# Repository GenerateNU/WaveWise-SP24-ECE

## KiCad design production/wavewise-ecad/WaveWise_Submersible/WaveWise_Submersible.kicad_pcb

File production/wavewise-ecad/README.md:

This is where all KiCAD stuff is stored

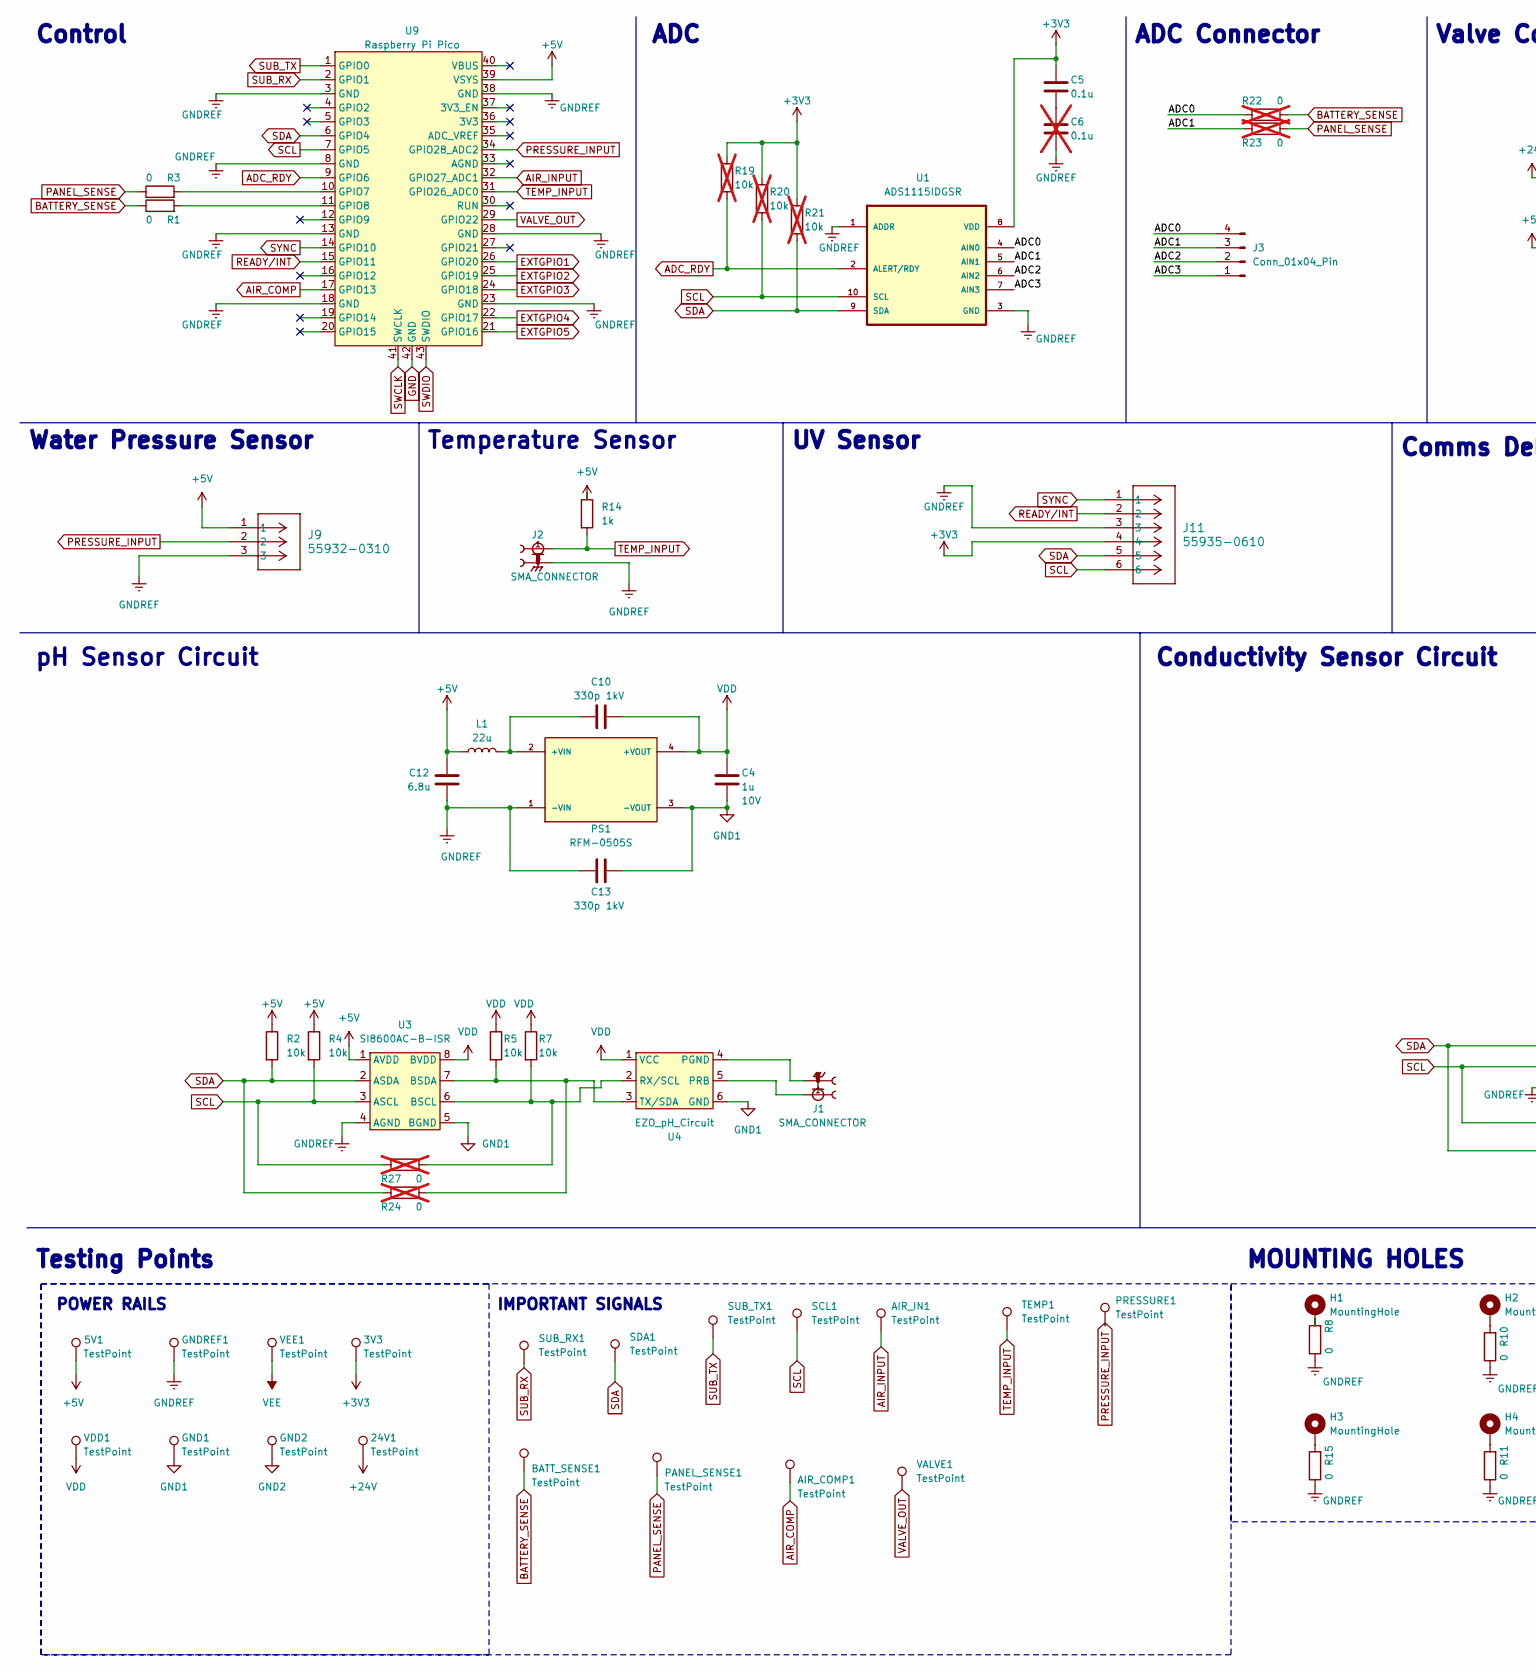
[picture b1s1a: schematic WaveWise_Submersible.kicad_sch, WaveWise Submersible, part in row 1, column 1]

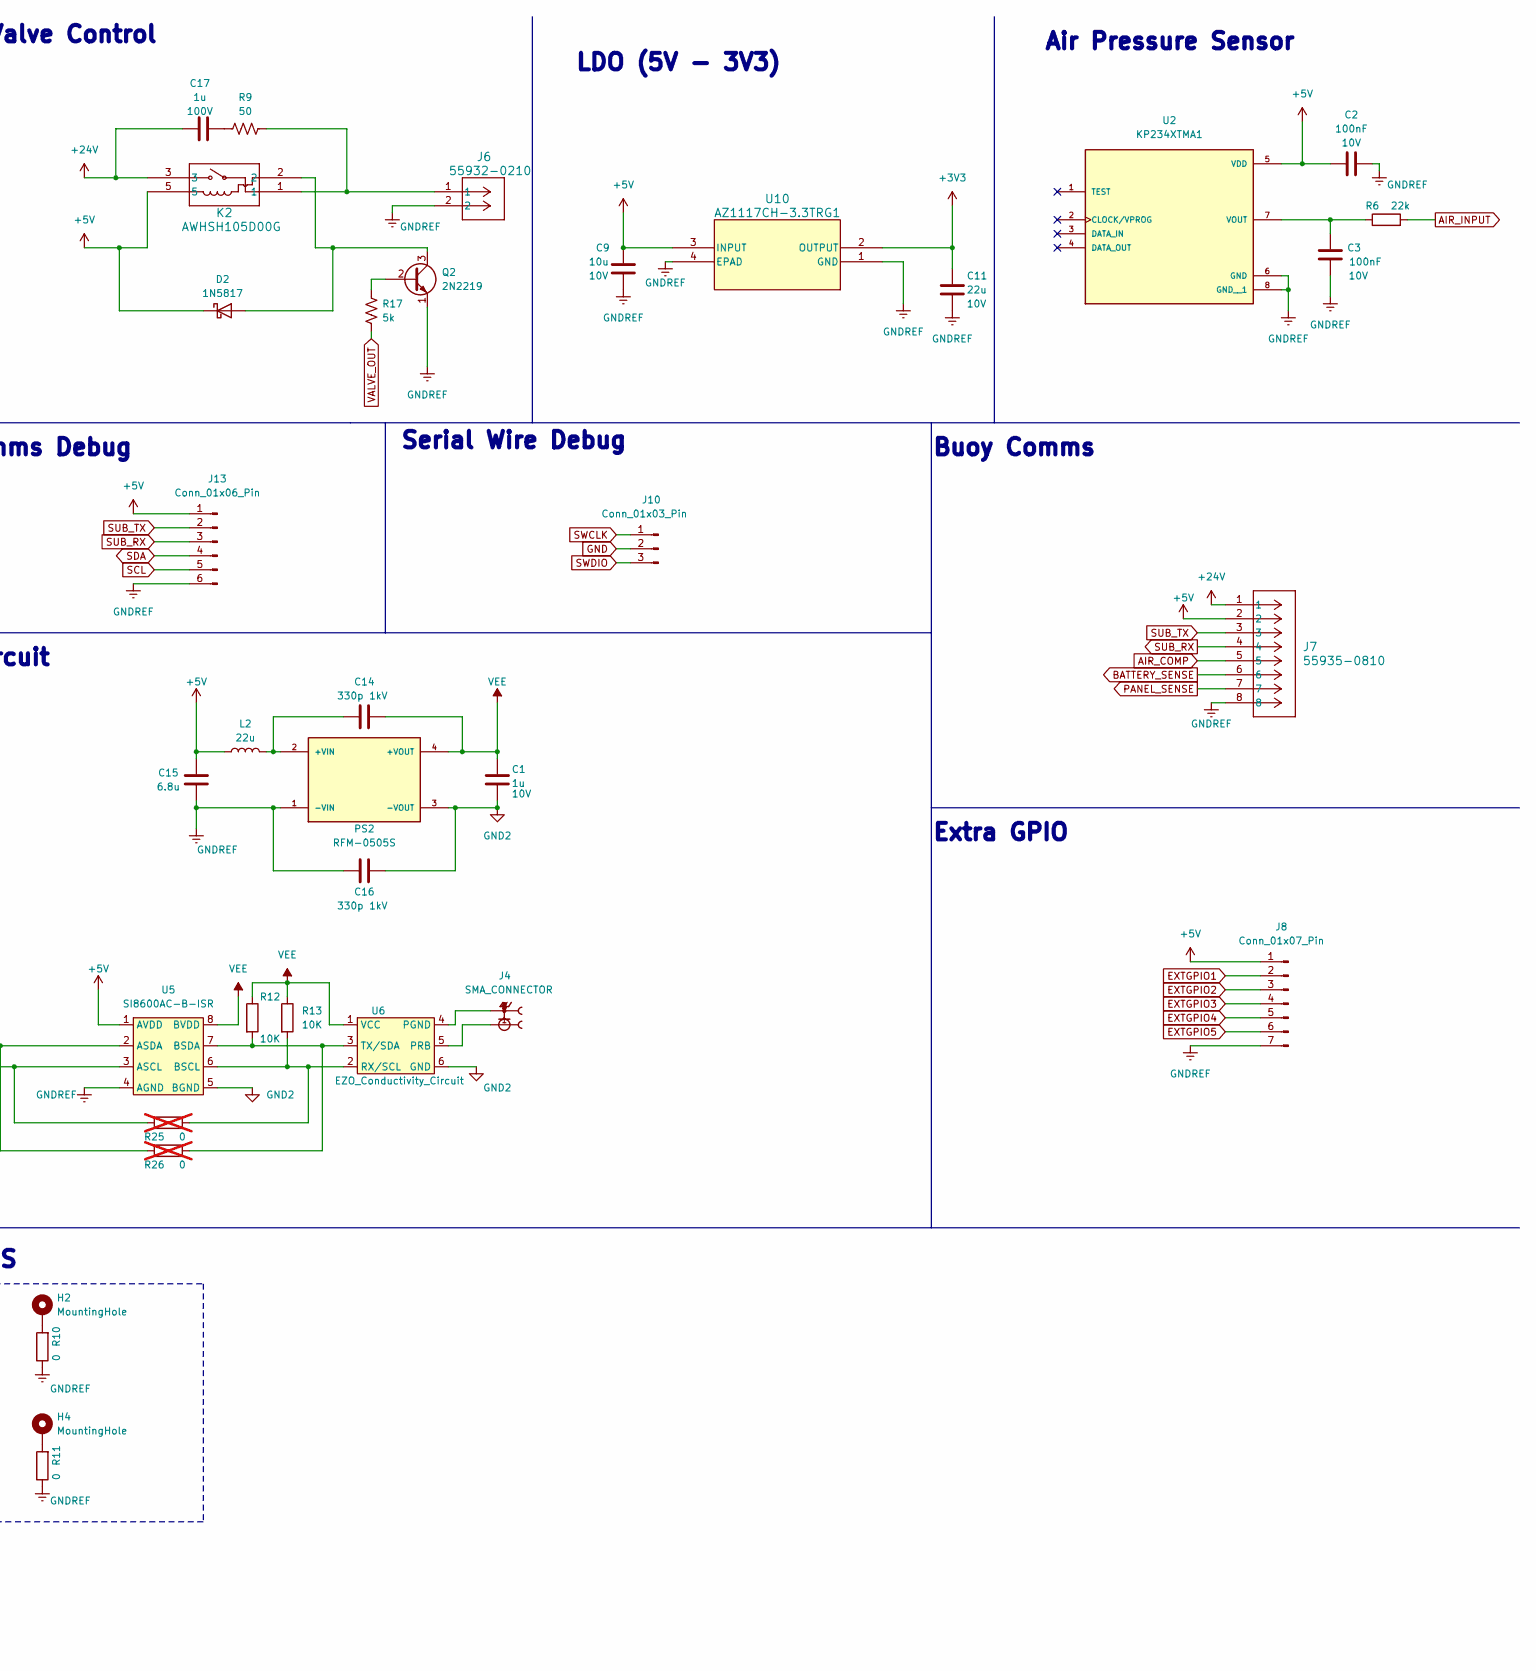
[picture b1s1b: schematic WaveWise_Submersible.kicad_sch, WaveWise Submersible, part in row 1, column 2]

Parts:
3V3, 5V1, 24V1: TestPoint; TestPoint_Pad_D1.5mm
AIR_COMP1: TestPoint; TestPoint_Pad_D1.5mm
AIR_IN1: TestPoint; TestPoint_Pad_D1.5mm
BATT_SENSE1: TestPoint; TestPoint_Pad_D1.5mm
C1, C4: 1u; C_0805_2012Metric; Voltage 10V
C2, C3: 100nF; C_0805_2012Metric; Voltage 10V
C5: 0.1u; C_0805_2012Metric
C6: 0.1u; C_0805_2012Metric; not fitted
C9: 10u; C_0805_2012Metric; Voltage 10V
C10, C13, C14, C16: 330p; C_0805_2012Metric; Voltage 1kV
C11: 22u; C_0805_2012Metric; Voltage 10V
C12, C15: 6.8u; C_0805_2012Metric
C17: 1u; C_0805_2012Metric; Voltage 100V
D2: 1N5817; D_DO-41_SOD81_P10.16mm_Horizontal
GND1, GND2: TestPoint; TestPoint_Pad_D1.5mm
GNDREF1: TestPoint; TestPoint_Pad_D1.5mm
H1, H2, H3, H4: MountingHole; MountingHole_3.2mm_M3_ISO7380_Pad
J1, J2, J4: SMA_CONNECTOR; SMA_Jack; PARTREV 1.3
J3: Conn_01x04_Pin; 61300411121
J6: 55932-0210; Molex_MicroClasp_55932-0210_1x02_P2.00mm_Vertical
J7: 55935-0810; Molex_MicroClasp_55935-0810_1x08_P2.00mm_Horizontal
J8: Conn_01x07_Pin; 61300711121
J9: 55932-0310; Molex_MicroClasp_55932-0310_1x03_P2.00mm_Vertical
J10: Conn_01x03_Pin; 61300311121
J11: 55935-0610; Molex_MicroClasp_55935-0610_1x06_P2.00mm_Horizontal
J13: Conn_01x06_Pin; 61300611121
K2: AWHSH105D00G
L1, L2: 22u; SRP6060FA220M
PANEL_SENSE1: TestPoint; TestPoint_Pad_D1.5mm
PRESSURE1: TestPoint; TestPoint_Pad_D1.5mm
PS1, PS2: RFM-0505S; PARTREV 0; DigiKey_Part_Number 945-3159-ND
Q2: 2N2219; TO-39-3
R1, R3, R8, R10, R11, R15: 0; R_0805_2012Metric
R2, R4, R5, R7: 10k; R_0805_2012Metric
R6: 22k; R_0805_2012Metric
R9: 50; R_0805_2012Metric
R12, R13: 10K; R_0805_2012Metric
R14: 1k; R_0805_2012Metric
R17: 5k; R_0805_2012Metric
R19, R20, R21: 10k; R_0805_2012Metric; not fitted
R22, R23, R24, R25, R26, R27: 0; R_0805_2012Metric; not fitted
SCL1: TestPoint; TestPoint_Pad_D1.5mm
SDA1: TestPoint; TestPoint_Pad_D1.5mm
SUB_RX1: TestPoint; TestPoint_Pad_D1.5mm
SUB_TX1: TestPoint; TestPoint_Pad_D1.5mm
TEMP1: TestPoint; TestPoint_Pad_D1.5mm
U1: ADS1115IDGSR; SOP50P490X110-10N
U2: KP234XTMA1; XDCR_KP234XTMA1; PARTREV 1.0
U3, U5: SI8600AC-B-ISR
U4: EZO_pH_Circuit
U6: EZO_Conductivity_Circuit
U9: Raspberry Pi Pico; RPi_Pico_SMD_TH
U10: AZ1117CH-3.3TRG1; SOT-223_DIO
VALVE1: TestPoint; TestPoint_Pad_D1.5mm
VDD1: TestPoint; TestPoint_Pad_D1.5mm
VEE1: TestPoint; TestPoint_Pad_D1.5mm

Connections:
+3V3: 3V3.1, C5.2, C11.1, J11.4, R19.1, R20.1, R21.1, U1.8 (VDD), U10.2 (OUTPUT)
+5V: 5V1.1, C2.1, C9.1, C12.1, C15.1, D2.1 (K), J7.2, J8.1, J9.1, J13.1, K2.5, L1.1, L2.1, R2.1, R4.1, R14.1, U2.5 (VDD), U3.1 (AVDD), U5.1 (AVDD), U9.39 (VSYS), U10.3 (INPUT)
+24V: 24V1.1, C17.2, J7.1, K2.3
/ADC0: J3.4, R22.1, U1.4 (AIN0)
/ADC1: J3.3, R23.1, U1.5 (AIN1)
/ADC2: J3.2, U1.6 (AIN2)
/ADC3: J3.1, U1.7 (AIN3)
ADC_RDY: R19.2, U1.2 (ALERT/RDY), U9.9 (GPIO6)
AIR_COMP: AIR_COMP1.1, J7.5, U9.17 (GPIO13)
AIR_INPUT: AIR_IN1.1, R6.2, U9.32 (GPIO27_ADC1)
BATTERY_SENSE: BATT_SENSE1.1, J7.6, R1.1, R22.2
EXTGPIO1: J8.2, U9.26 (GPIO20)
EXTGPIO2: J8.3, U9.25 (GPIO19)
EXTGPIO3: J8.4, U9.24 (GPIO18)
EXTGPIO4: J8.5, U9.22 (GPIO17)
EXTGPIO5: J8.6, U9.21 (GPIO16)
GND: J10.2, U9.42 (GND)
GND1: C4.2, C13.1, GND1.1, PS1.3 (-VOUT), U3.5 (BGND), U4.6 (GND)
GND2: C1.2, C16.1, GND2.1, PS2.3 (-VOUT), U5.5 (BGND), U6.6 (GND)
GNDREF: C2.2, C3.2, C6.1, C9.2, C11.2, C12.2, C13.2, C15.2, C16.2, GNDREF1.1, J2.2, J2.3, J2.4, J2.5, J6.2, J7.8, J8.7, J9.3, J11.3, J13.6, PS1.1 (-VIN), PS2.1 (-VIN), Q2.1 (E), R8.1, R10.1, R11.1, R15.1, U1.1 (ADDR), U1.3 (GND), U2.6 (GND), U2.8 (GND__1), U3.4 (AGND), U5.4 (AGND), U9.3 (GND), U9.8 (GND), U9.13 (GND), U9.18 (GND), U9.23 (GND), U9.28 (GND), U9.38 (GND), U10.1 (GND), U10.4 (EPAD)
unnamed: C5.1, C6.2
unnamed: C17.1, R9.1
unnamed: D2.2 (A), K2.2, Q2.3 (C)
unnamed: H1.1, R8.2
unnamed: H2.1, R10.2
unnamed: H3.1, R15.2
unnamed: H4.1, R11.2
unnamed: J6.1, K2.1, R9.2
unnamed: C10.2, L1.2, PS1.2 (+VIN)
unnamed: C14.2, L2.2, PS2.2 (+VIN)
unnamed: Q2.2 (B), R17.2
unnamed: C3.1, R6.1, U2.7 (VOUT)
unnamed: R7.2, R27.2, U3.6 (BSCL), U4.2 (RX/SCL)
unnamed: R5.2, R24.2, U3.7 (BSDA), U4.3 (TX/SDA)
unnamed: J1.2, J1.3, J1.4, J1.5, U4.4 (PGND)
unnamed: J1.1, U4.5 (PRB)
unnamed: R13.2, R25.2, U5.6 (BSCL), U6.2 (RX/SCL)
unnamed: R12.2, R26.2, U5.7 (BSDA), U6.3 (TX/SDA)
unnamed: J4.2, J4.3, J4.4, J4.5, U6.4 (PGND)
unnamed: J4.1, U6.5 (PRB)
unnamed: R3.2, U9.10 (GPIO7)
unnamed: R1.2, U9.11 (GPIO8)
PANEL_SENSE: J7.7, PANEL_SENSE1.1, R3.1, R23.2
PRESSURE_INPUT: J9.2, PRESSURE1.1, U9.34 (GPIO28_ADC2)
READY/INT: J11.2, U9.15 (GPIO11)
SCL: J11.6, J13.5, R4.2, R20.2, R25.1, R27.1, SCL1.1, U1.10 (SCL), U3.3 (ASCL), U5.3 (ASCL), U9.7 (GPIO5)
SDA: J11.5, J13.4, R2.2, R21.2, R24.1, R26.1, SDA1.1, U1.9 (SDA), U3.2 (ASDA), U5.2 (ASDA), U9.6 (GPIO4)
SUB_RX: J7.4, J13.3, SUB_RX1.1, U9.2 (GPIO1)
SUB_TX: J7.3, J13.2, SUB_TX1.1, U9.1 (GPIO0)
SWCLK: J10.1, U9.41 (SWCLK)
SWDIO: J10.3, U9.43 (SWDIO)
SYNC: J11.1, U9.14 (GPIO10)
TEMP_INPUT: J2.1, R14.2, TEMP1.1, U9.31 (GPIO26_ADC0)
VALVE_OUT: R17.1, U9.29 (GPIO22), VALVE1.1
VDD: C4.1, C10.1, PS1.4 (+VOUT), R5.1, R7.1, U3.8 (BVDD), U4.1 (VCC), VDD1.1
VEE: C1.1, C14.1, PS2.4 (+VOUT), R12.1, R13.1, U5.8 (BVDD), U6.1 (VCC), VEE1.1

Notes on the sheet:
Control
Comms Debug
Conductivity Sensor Circuit
Buoy Comms
ADC Connector
UV Sensor
LDO (5V - 3V3)
IMPORTANT SIGNALS
Temperature Sensor
POWER RAILS
Valve Control
Extra GPIO
pH Sensor Circuit
ADC
Serial Wire Debug
Air Pressure Sensor
MOUNTING HOLES
Water Pressure Sensor
Testing Points

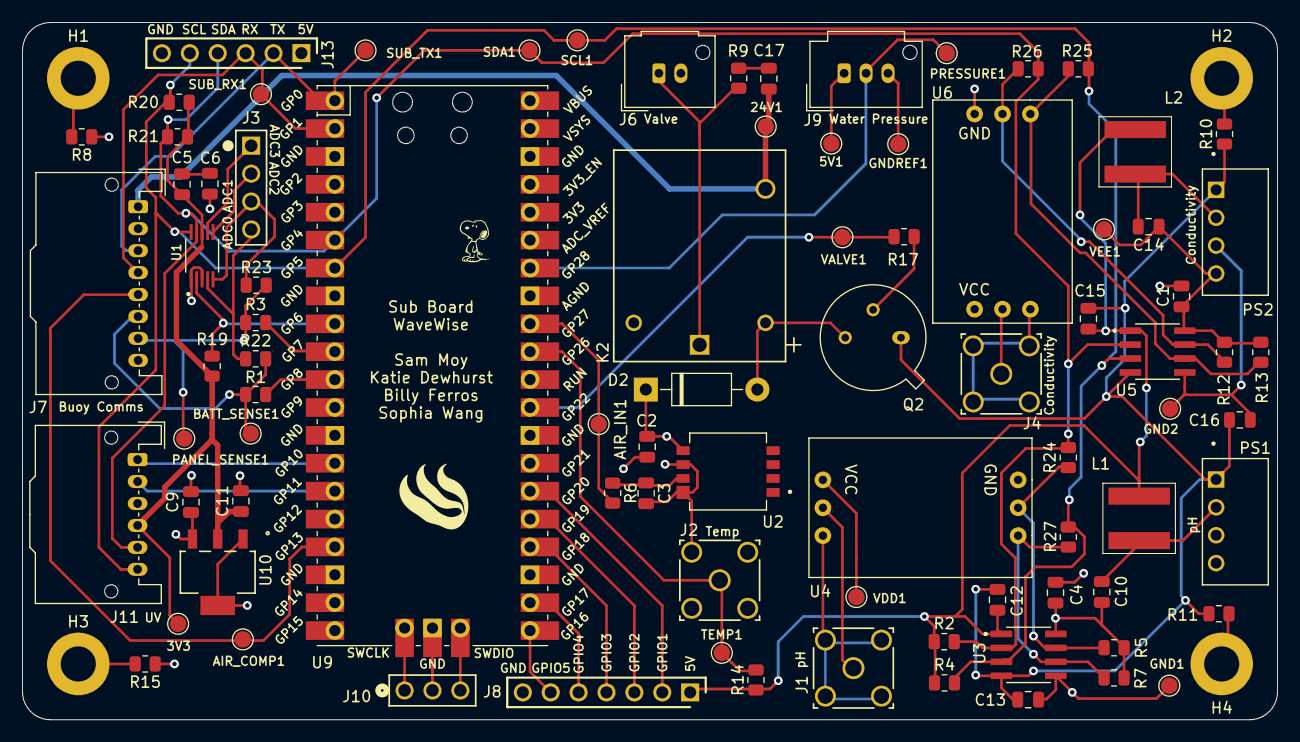
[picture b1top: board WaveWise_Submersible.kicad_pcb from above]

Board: 4 copper layers, 114.3 x 63.5 mm, 89 parts (0 on the bottom side), 56 nets.

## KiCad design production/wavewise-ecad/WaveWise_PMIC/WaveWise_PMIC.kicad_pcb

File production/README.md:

# Production
This directory is for code/schematics/layouts that will be implemented in the final prototype.

> **_NOTE:_** If you have code to test out a component/subsystem, it should probably go into ```/testing```

## Directory Structure:
```
.
|───wavewise-ecad    # contains any schematic/board development files
|
└───wavewise-src     # contains any embedded code or important scripts
```

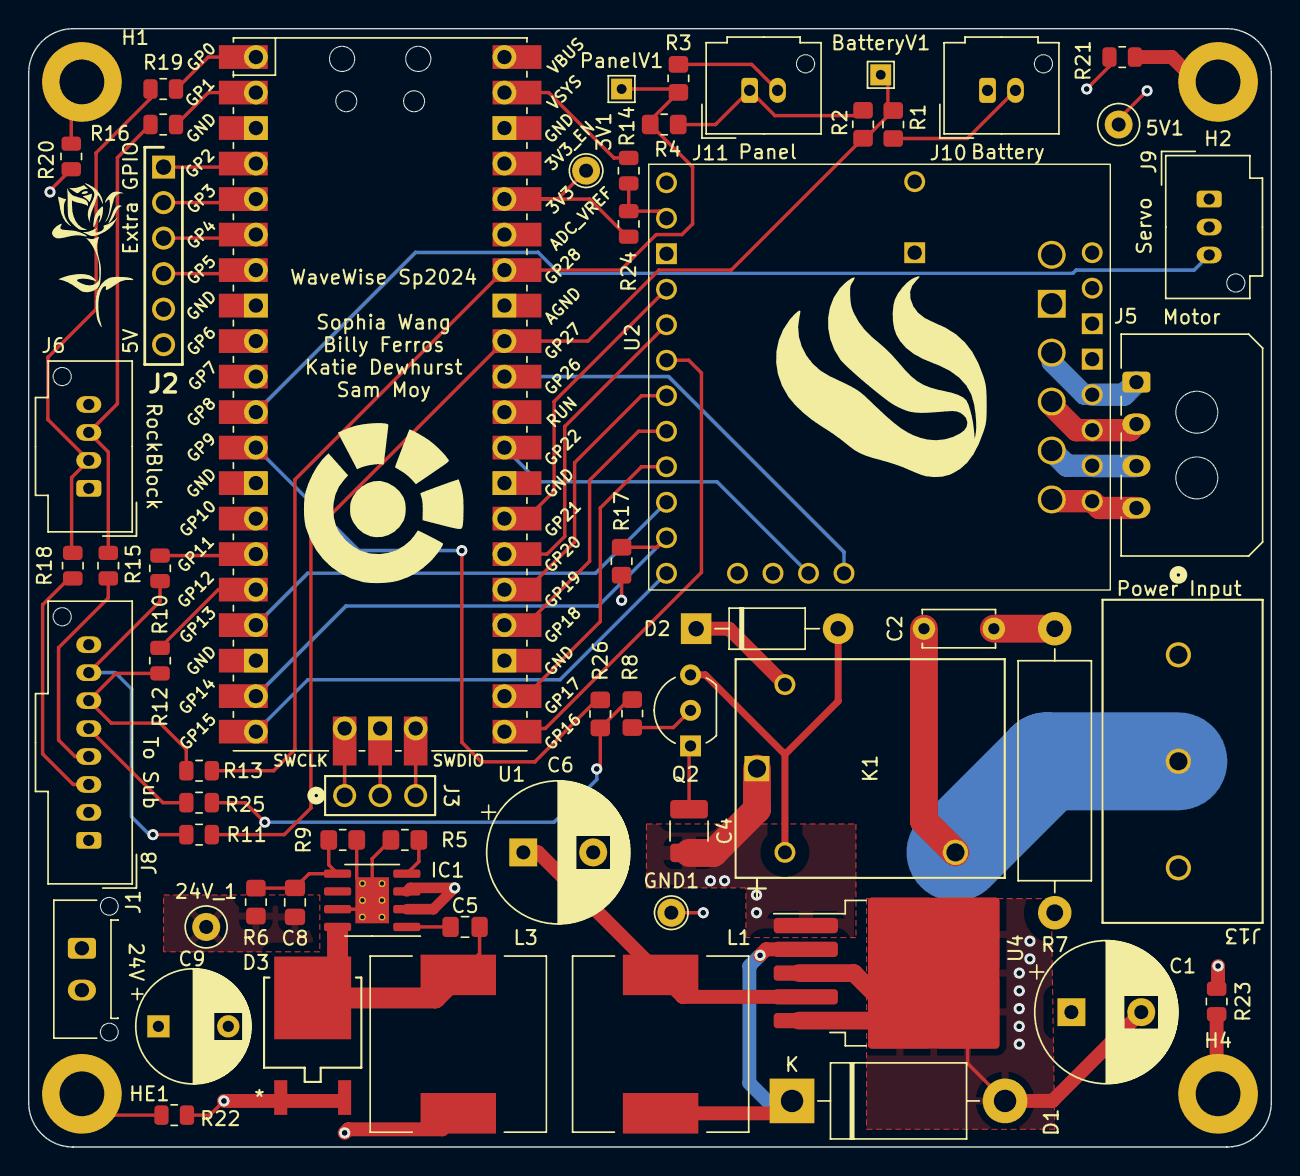
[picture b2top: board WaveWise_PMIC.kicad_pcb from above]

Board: 4 copper layers, 88.9 x 80.0 mm, 67 parts (0 on the bottom side), 58 nets.

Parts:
3V1: TestPoint; TestPoint_THTPad_D2.0mm_Drill1.0mm
5V1: 5V TP; TestPoint_Loop_D1.80mm_Drill1.0mm_Beaded
24V_1: 24V TP; TestPoint_Loop_D1.80mm_Drill1.0mm_Beaded
BatteryV1: TestPoint; TestPoint_THTPad_1.5x1.5mm_Drill0.7mm
C1: 100u/80V; CP_Radial_D10.0mm_P5.00mm
C2: 1uF/100V; C_Disc_D5.0mm_W2.5mm_P5.00mm
C4: 2.2u/100V; C_1210_3225Metric_Pad1.33x2.70mm_HandSolder
C5: 100n/25V; C_0805_2012Metric_Pad1.18x1.45mm_HandSolder
C6: 1000u/10V; CP_Radial_D10.0mm_P5.00mm
C8: 560p/50V; C_0805_2012Metric_Pad1.18x1.45mm_HandSolder
C9: 120u/50V; CP_Radial_D8.0mm_P5.00mm
D1: 1N5822; D_DO-201AD_P15.24mm_Horizontal
D2: 1N5817; D_DO-41_SOD81_P10.16mm_Horizontal
D3: SBR10200CTL-13; TO-252DPAK_DIO
G1, G2: LOGO
GND1: TestPoint; TestPoint_THTPad_D2.0mm_Drill1.0mm
Ge: LOGO
H1, H2, H4: MountingHole; MountingHole_3.2mm_M3_ISO7380_Pad
HE1: MountingHole; MountingHole_3.2mm_M3_ISO7380_Pad
IC1: LV14360PDDAR; SOIC-8-1EP_3.9x4.9mm_P1.27mm_EP2.41x3.3mm_ThermalVias
J1: 5031590200; Molex_Micro-Fit_3.0_43650-0215_1x02_P3.00mm_Vertical
J2: Conn_01x06_Pin; 61300611121
J3: Conn_01x03_Pin; 61300311121
J5: 5031590400; Molex_Micro-Fit_3.0_43650-0400_1x04_P3.00mm_Horizontal
J6: 5031590400; Molex_MicroClasp_55932-0410_1x04_P2.00mm_Vertical
J8: 5031590800; Molex_MicroClasp_55932-0810_1x08_P2.00mm_Vertical
J9: 5031590300; Molex_MicroClasp_55932-0310_1x03_P2.00mm_Vertical
J10, J11: 5031590200; Molex_MicroClasp_55932-0210_1x02_P2.00mm_Vertical
J13: Screw_Terminal_01x03; CONN_1731734_PXC
K1: AWHSH105D00G
L1: 100u; L_12x12mm_H6mm
L3: 27u; L_12x12mm_H6mm
PanelV1: TestPoint; TestPoint_THTPad_1.5x1.5mm_Drill0.7mm
Q2: 2N2219; TO-92_Inline_Wide
R1: 340k; R_0805_2012Metric_Pad1.20x1.40mm_HandSolder
R2: 20k; R_0805_2012Metric_Pad1.20x1.40mm_HandSolder
R3: 500k; R_0805_2012Metric_Pad1.20x1.40mm_HandSolder
R4: 17k; R_0805_2012Metric_Pad1.20x1.40mm_HandSolder
R5: 45.3k; R_0805_2012Metric_Pad1.20x1.40mm_HandSolder
R6: 316k; R_0805_2012Metric_Pad1.20x1.40mm_HandSolder
R7: 50; R_Axial_DIN0516_L15.5mm_D5.0mm_P20.32mm_Horizontal
R8: 5k; R_0805_2012Metric_Pad1.20x1.40mm_HandSolder
R9: 10.2k; R_0805_2012Metric_Pad1.20x1.40mm_HandSolder
R10, R11, R12, R13, R14, R15, R16, R18, R19, R20, R21, R22, R23, R24, R25: 0; R_0805_2012Metric
R17: 10k; R_0805_2012Metric_Pad1.20x1.40mm_HandSolder
R26: 0; R_0805_2012Metric_Pad1.20x1.40mm_HandSolder
U1: Raspberry Pi Pico; Pico
U2: Pololu_DRV8711_Motor_Driver; POLOLU_36v4
U4: LM2576HVS-5.0_NOPB; TO-263-5_TabPin6

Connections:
+3.3V: 3V1.1, R24.2, U1.36 (3V3)
+5V: 5V1.1, C6.1, D2.1 (K), J2.6, J6.4, J8.2, J9.1, K1.5, L1.2, R14.2, U1.39 (VSYS), U4.4 (FB)
+24V: 24V_1.1, C8.2, C9.1, J1.2, J8.1, L3.2, R6.1
+48V: C1.1, C4.1, IC1.2 (VIN), IC1.3 (EN), J13.3, K1.1, R7.2, U2.1 (Vin), U4.1 (VIN)
+BATT: J10.2, R1.1
/AOUT1: J5.1, U2.2 (AOUT1)
/AOUT2: J5.2, U2.3 (AOUT2)
/BOUT1: J5.3, U2.4 (BOUT1)
/BOUT2: J5.4, U2.5 (BOUT2)
/Connectors/BATT_SENSE_DIO: R10.2, U1.15 (GPIO11)
/Connectors/BICO_UART_RX: R16.1, U1.2 (GPIO1)
/Connectors/BICO_UART_TX: R19.2, U1.1 (GPIO0)
/Connectors/Batt V Sense: BatteryV1.1, R1.2, R2.1, R11.2, U1.32 (GPIO27_ADC1)
/Connectors/GPIO1: J2.1, U1.4 (GPIO2)
/Connectors/GPIO2: J2.2, U1.5 (GPIO3)
/Connectors/GPIO3: J2.3, U1.6 (GPIO4)
/Connectors/GPIO4: J2.4, U1.7 (GPIO5)
/Connectors/PANEL_SENSE_DIO: R12.2, U1.16 (GPIO12)
/Connectors/PWM_Servo: J9.3, U1.11 (GPIO8)
/Connectors/Panel V Sense: PanelV1.1, R3.2, R4.1, R13.2, U1.34 (GPIO28_ADC2)
/Connectors/SICO_PUMP_CONTROL: J8.5, R25.2
/Connectors/SICO_RX: J8.4, R15.2
/Connectors/SICO_TX: J8.3, R18.2
/Connectors/SWCLK: J3.1, U1.41 (SWCLK)
/Connectors/SWDIO: J3.3, U1.43 (SWDIO)
/Connectors/rockblock_RX: J6.3, R15.1, R16.2
/Connectors/rockblock_TX: J6.2, R18.1, R19.1
/Inverter_Input: C2.2, J13.2, K1.3
/PICO (BICO)/BICO_PUMP_CTRL: R26.1, U1.12 (GPIO9)
/PICO (BICO)/MOTOR_BEMF: U1.31 (GPIO26_ADC0), U2.6 (BEMF)
/PICO (BICO)/MOTOR_DIR/AIN2: U1.26 (GPIO20), U2.17 (DIR)
/PICO (BICO)/MOTOR_FLT: U1.20 (GPIO15), U2.10 (~FLT)
/PICO (BICO)/MOTOR_RESET: R17.1, U1.19 (GPIO14), U2.11 (RST)
/PICO (BICO)/MOTOR_SLP: U1.17 (GPIO13), U2.12 (~SLP)
/PICO (BICO)/MOTOR_SPI0_CSn: U1.22 (GPIO17), U2.13 (SCS)
/PICO (BICO)/MOTOR_SPI0_RX: U1.21 (GPIO16), U2.16 (SDATO)
/PICO (BICO)/MOTOR_SPI0_SCK: U1.24 (GPIO18), U2.14 (SCLK)
/PICO (BICO)/MOTOR_SPI0_TX: U1.25 (GPIO19), U2.15 (SDATI)
/PICO (BICO)/MOTOR_STALL: U1.29 (GPIO22), U2.7 (~STALL)
/PICO (BICO)/MOTOR_STEP/AIN1: U1.27 (GPIO21), U2.18 (STEP)
/PUMP_CONTROL: R8.1, R25.1, R26.2
/Pneumatic Control/ICREF: R14.1, R24.1, U2.19 (ICREF)
GND: C1.2, C4.2, C6.2, C9.2, D1.2 (A), D3.1 (ANODE_1), D3.3 (ANODE_2), GND1.1, IC1.7 (GND), IC1.9 (EP), J1.1, J2.5, J3.2, J6.1, J8.8, J9.2, J10.1, J11.1, J13.1, Q2.1 (E), R2.2, R4.2, R5.2, R9.2, R17.2, R20.1, R21.1, R22.1, R23.1, U1.3 (GND), U1.8 (GND), U1.13 (GND), U1.18 (GND), U1.23 (GND), U1.28 (GND), U1.33 (AGND), U1.38 (GND), U1.42 (GND), U2.22 (GND), U4.3 (GND), U4.5 (ON/OFF), U4.6 (GND)
unnamed: C2.1, R7.1
unnamed: D1.1 (K), L1.1, U4.2 (OUT)
unnamed: D2.2 (A), K1.2, Q2.3 (C)
unnamed: C5.2, D3.2 (CATHODE), IC1.8 (SW), L3.1
unnamed: H1.1, R20.2
unnamed: H2.1, R21.2
unnamed: H4.1, R23.2
unnamed: HE1.1, R22.2
unnamed: C5.1, IC1.1 (BOOT)
unnamed: C8.1, IC1.5 (FB), R6.2, R9.1
unnamed: IC1.4 (RT/SYNC), R5.1
unnamed: Q2.2 (B), R8.2
VBUS: J11.2, R3.1
batt_sense: J8.7, R10.1, R11.1
panel_sense: J8.6, R12.1, R13.1

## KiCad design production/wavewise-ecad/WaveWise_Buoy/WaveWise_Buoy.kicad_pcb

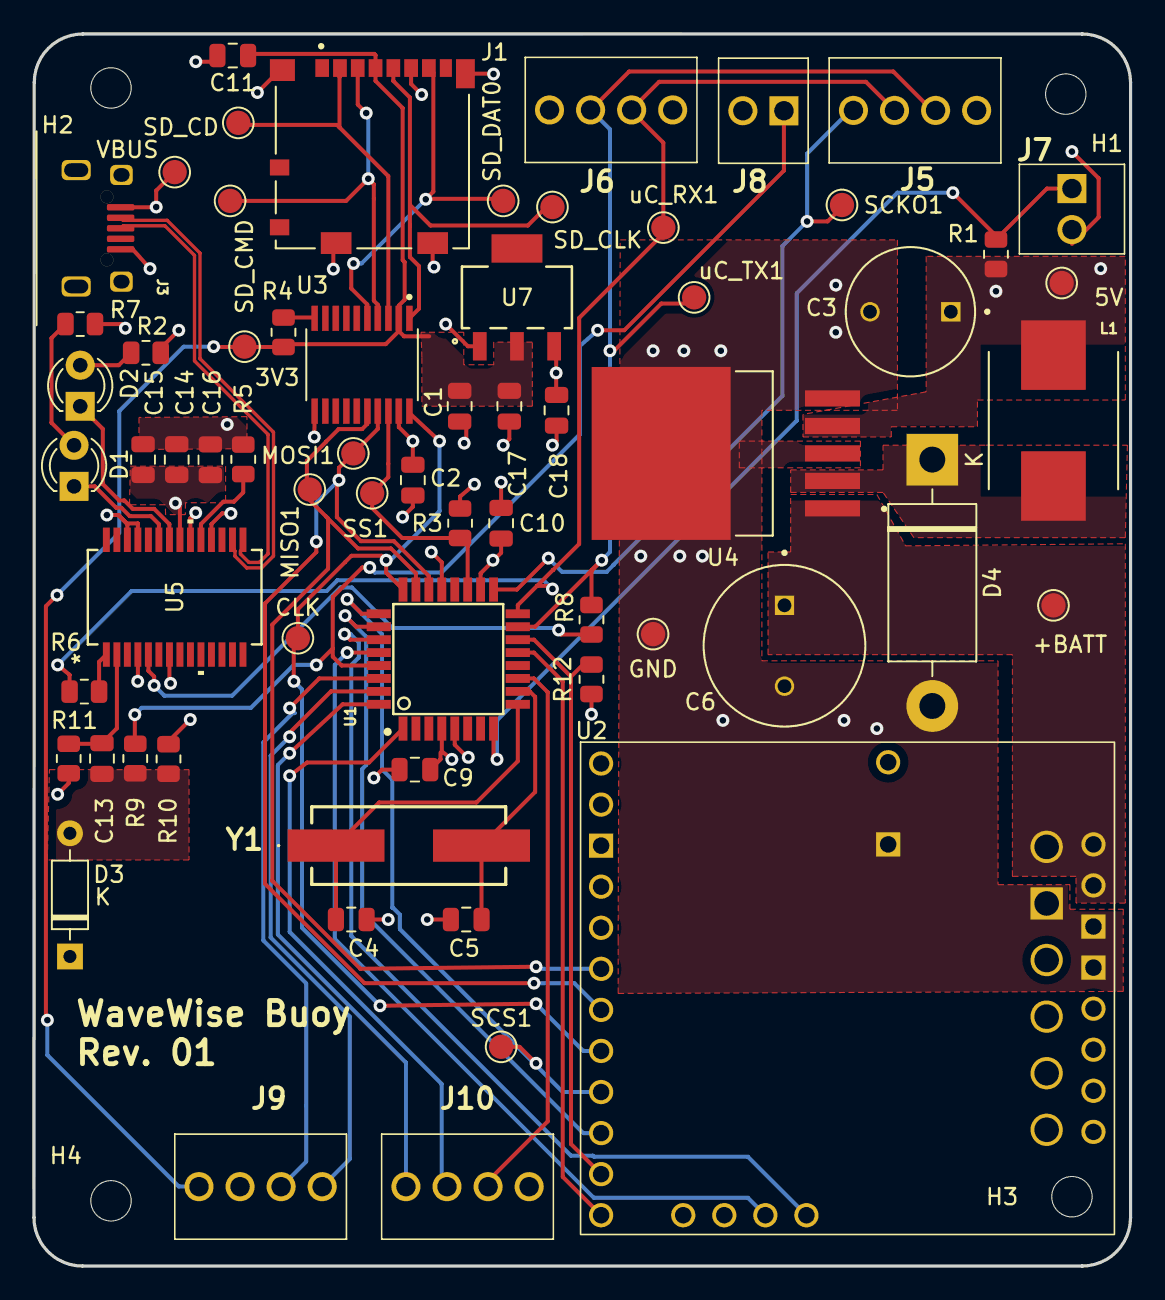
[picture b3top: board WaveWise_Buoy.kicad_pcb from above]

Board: 4 copper layers, 67.8 x 76.2 mm, 68 parts (0 on the bottom side), 43 nets.

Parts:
3V3, 5V: TestPoint; TestPoint_Pad_D1.5mm
+BATT: TestPoint; TestPoint_Pad_D1.5mm
C1, C2: 0.1u/10V; C_0805_2012Metric
C3: 1000u/10V; 1000uF_10V_Cap
C4, C5: 22pF/10V; C_0805_2012Metric
C6: 100u/80V; 100uF_80V_Cap
C9, C10, C13, C14, C15: 100n/10V; C_0805_2012Metric
C11: 0.1u/5V; C_0805_2012Metric
C16: 4.7u/10V; C_0805_2012Metric
C17: 22u/10V; C_0805_2012Metric
C18: 10u/10V; C_0805_2012Metric
CLK: TestPoint; TestPoint_Pad_D1.5mm
D1, D2: LED_S; LED_D3.0mm
D3: 1N4448; D_DO-35_SOD27_P7.62mm_Horizontal
D4: 1N5822; D_DO-201AD_P15.24mm_Horizontal
GND: TestPoint; TestPoint_Pad_D1.5mm
H1, H2, H3, H4: MountingHole; MountingHole_2.5mm
J1: 104031-0811; SD_Mount
J3: USB_B_Micro; MicroUSB_Mount
J5, J6, J9, J10: Screw_Terminal_01x04; ScrewTerminal_01x04_2.54mm
J7, J8: Screw_Terminal_01x02; ScrewTerminal_01x02_2.54mm
L1: 100u; IND_ETQP5M101YGK
MISO1: TestPoint; TestPoint_Pad_D1.5mm
MOSI1: TestPoint; TestPoint_Pad_D1.5mm
R1, R3, R5, R10, R12: 10k; R_0805_2012Metric
R2, R7: 100; R_0805_2012Metric
R4: 47k; R_0805_2012Metric
R6, R8, R11: 1k; R_0805_2012Metric
R9: 0; R_0805_2012Metric
SCKO1: TestPoint; TestPoint_Pad_D1.5mm
SCS1: TestPoint; TestPoint_Pad_D1.5mm
SD_CD: TestPoint; TestPoint_Pad_D1.5mm
SD_CLK: TestPoint; TestPoint_Pad_D1.5mm
SD_CMD: TestPoint; TestPoint_Pad_D1.5mm
SD_DAT0: TestPoint; TestPoint_Pad_D1.5mm
SS1: TestPoint; TestPoint_Pad_D1.5mm
U1: ATMEGA328PB-ANR
U2: Pololu_DRV8711_Motor_Driver; POLOLU_36v4
U3: TXB0108PWR; SOP65P640X120-20N
U4: LM2576HVS-5.0_NOPB; LM2576S-12_NOPB
U5: FT232RL-REEL; IC28_SSOP-28_FTD
U7: AZ1117CH-3.3TRG1; SOT-223_DIO
VBUS: TestPoint; TestPoint_Pad_D1.5mm
Y1: AS-16.000-20-SMD-TR; AS1600020SMDTR
uC_RX1: TestPoint; TestPoint_Pad_D1.5mm
uC_TX1: TestPoint; TestPoint_Pad_D1.5mm

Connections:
+3V3: 3V3.1, C1.1, C11.1, C17.1, J1.4 (VDD), J9.1, R4.2, U3.2 (VCCA), U7.2 (OUTPUT)
+5V: 5V.1, C2.1, C3.P, C9.1, C10.1, C14.1, C15.1, C16.1, C18.1, D3.1 (K), J3.1 (VBUS), J5.1, J6.1, J9.2, L1.1, R1.1, R2.1, R3.1, R5.1, R7.1, R10.2, U1.4 (VCC), U1.18 (AVCC), U3.19 (VCCB), U4.4 (FB), U5.4 (VCCIO), U5.20 (VCC), U7.3 (INPUT), VBUS.1
+BATT: +BATT.1, C6.P, U2.1 (Vin), U4.1 (VIN)
BEMF: U1.27 (PC4), U2.6 (BEMF)
BUTTON: J7.1, R1.2, U1.8 (PB7)
CLK: CLK.1, U1.24 (PC1), U2.14 (SCLK), U3.20 (B1)
D+: J3.3 (D+), U5.15 (USBDP)
D-: J3.2 (D-), U5.16 (USBDM)
EXTGPIO1: J9.3, U1.30 (PD0)
EXTGPIO2: J9.4, U1.31 (PD1)
EXTGPIO3: J10.1, U1.32 (PD2)
EXTGPIO4: J10.2, U1.1 (PD3)
EXTGPIO5: J10.3, U1.11 (PD7)
GND: C1.2, C2.2, C3.N, C4.1, C5.2, C6.N, C9.2, C10.2, C11.2, C14.2, C15.2, C16.2, C17.2, C18.2, D4.2 (A), GND.1, J1.6 (VSS), J1.G1 (GND), J1.G2 (GND), J1.G3 (GND), J1.G4 (GND), J3.5 (GND), J3.6 (Shield), J6.4, J7.2, J8.2, J10.4, R11.1, R12.2, U1.5 (GND), U1.21 (GND), U2.22 (GND), U3.11 (GND), U4.3 (GND), U4.5 (ON/OFF), U4.6 (GND), U5.7 (GND), U5.18 (GND), U5.21 (GND), U5.25 (AGND), U5.26 (TEST), U7.1 (ADJ/GND)
MISO1: MISO1.1, U1.23 (MISO1), U2.16 (SDATO), U3.16 (B4)
MOSI1: MOSI1.1, U1.22 (MOSI1), U2.15 (SDATI), U3.17 (B3)
unnamed: D1.2 (A), R7.2
unnamed: D1.1 (K), U5.23 (CBUS0)
unnamed: D2.2 (A), R2.2
unnamed: D2.1 (K), U5.22 (CBUS1)
unnamed: C13.2, D3.2 (A), R9.1, R10.1
unnamed: D4.1 (K), L1.2, U4.2 (OUT)
unnamed: C4.2, U1.9 (PD5), Y1.1
unnamed: C5.1, U1.10 (PD6), Y1.2
unnamed: R4.1, U3.10 (OE)
unnamed: C13.1, R11.2, U5.2 (DTR#)
unnamed: R5.2, U5.19 (RESET#)
unnamed: R8.2, U5.5 (RXD)
unnamed: R6.1, U5.1 (TXD)
RESET: J8.1, R9.2, U1.29 (PC6/~RESET)
SCK0: J5.4, SCKO1.1, U1.17 (PB5)
SCS: SCS1.1, U1.25 (PC2), U2.13 (SCS)
SD_CD: J1.2 (CD/DAT3), SD_CD.1, U3.3 (A2)
SD_CLK: J1.5 (CLK), SD_CLK.1, U3.1 (A1)
SD_CMD: J1.3 (CMD), SD_CMD.1, U3.4 (A3)
SD_DAT0: J1.7 (DAT0), SD_DAT0.1, U3.5 (A4)
SS1: R3.2, SS1.1, U1.19 (~SS1), U3.18 (B2)
STALL: U1.28 (PC5), U2.7 (~STALL)
uC_RX: J5.3, J6.3, R6.2, U1.16 (MISO0/RX), uC_RX1.1
uC_TX: J5.2, J6.2, R8.1, U1.15 (MOSI0/TX), uC_TX1.1
~MTR_FAULT: U1.13 (PB1), U2.10 (~FLT)
~MTR_RST: R12.1, U1.14 (PB2), U2.11 (RST)
~SLP: U1.26 (PC3), U2.12 (~SLP)

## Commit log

2024-01-16 add previous wavewise stuff
2024-02-04 create backups
2024-02-13 Add Power Management IC Board
2024-02-20 Create Lift Control Schematic for Katie
2024-02-21 sub schematic draft
2024-02-22 added Pico symbol/footprint/3D model
2024-02-22 Update WaveWise_Submersible.kicad_sch
    Changed valve control circuit in sub schematic
2024-02-22 updated mosfet circuit
2024-02-22 added jst connectors
2024-02-22 rev 1 before merging
    lift control rip
2024-02-22 Power Board Rev 1
    Power board completed without Buck coverters
2024-02-23 changed header pins/valve control
2024-02-23 Create Hierarchical Structure to PMIC Board
2024-02-26 Added Buck converters
2024-02-26 Added connectors and pico
2024-02-27 added 2 to 7 pin molex clik-mate connectors
2024-02-27 add control stuff
2024-03-14 Added some footprints not all yet though
    Footprint addition 3/14/2024
2024-03-16 Added more footprints and changed 24V buck shottky diode schematic diagram
2024-03-16 updated root and adding connectors
2024-03-18 adding more to root page and updating for battery sensing
2024-03-18 Started PCB
2024-03-22 layout first draft, added general/connector footprint
2024-03-22 added most footprints still need polulu footprint
2024-03-25 move to archive
2024-03-25 More stuff done to PCB Added polulu
2024-03-26 Sub layout draft 2 for chiefs
2024-03-26 Rearranged the whole board
    All done aside from no place resistor and power planes
2024-03-27 more change
2024-03-27 Completed all connections and added mounting holes
    Needs some review with the DRC tool
2024-03-28 Prelim board layout
2024-03-28 fix drc
2024-03-28 power stuff
2024-03-29 Sub pcb draft 3
2024-03-29 add silkscreen
2024-03-29 change pins on pico for layout
2024-03-29 add back in 24V output
2024-03-29 change 24V from microclasp to microfit
2024-03-29 add gerber files
2024-03-31 change sub vias to through and create step file for pmic
2024-03-31 uart comm for rb
2024-04-08 create file structure
2024-04-13 create test programs for sensors
2024-04-13 create html bom
2024-04-14 adding pneumatic controls code
2024-04-16 pool test
2024-04-16 added valve/air comp control main.py uploaded to sub pico
2024-04-18 added uv sensor program
2024-05-24 final materials
